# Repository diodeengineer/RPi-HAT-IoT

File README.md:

### RPi-HAT-IoT
A custom Raspberry Pi HAT designed for high-performance IoT applications. This board simplifies the integration of sensors and connectivity, turning a standard Raspberry Pi into a robust IoT Gateway or Edge device.

### Overview
This project provides a hardware-level expansion for the Raspberry Pi 40-pin header. It is designed to bridge the gap between physical sensors and cloud-based IoT platforms.

### Features
Form Factor: Standard Raspberry Pi HAT (compatible with Pi 3, 4, and 5).

Sensor Suite: (e.g., Temperature, Humidity, and Pressure sensors).

Indicator: Status LEDs for power and data transmission.

### 📂 Project Structure
/Hardware: KiCad schematic and PCB layout files.

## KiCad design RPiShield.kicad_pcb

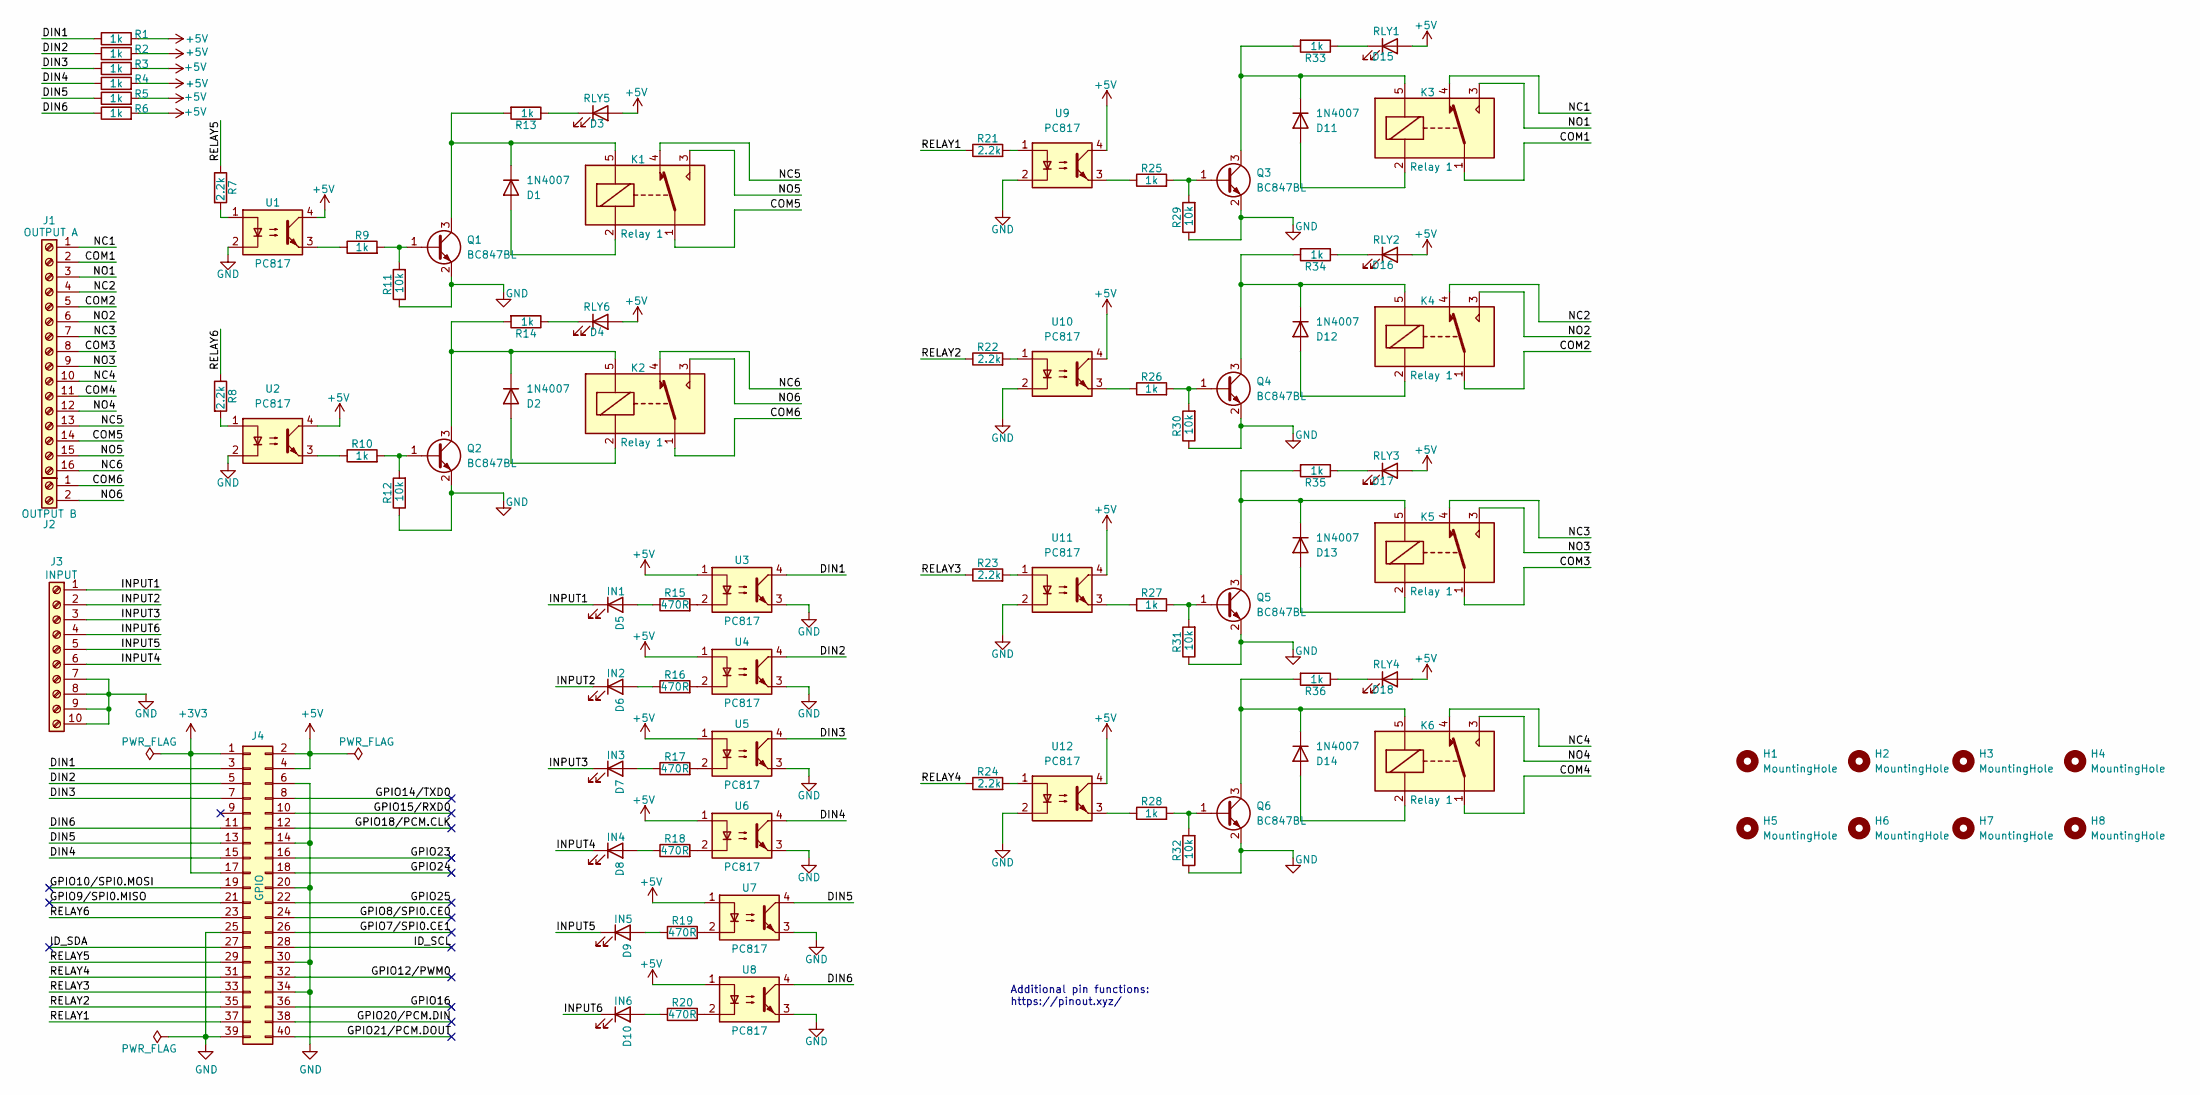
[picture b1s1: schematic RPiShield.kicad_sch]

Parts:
D1, D2, D11, D12, D13, D14: 1N4007; D_SMA_Handsoldering
D3: RLY5; LED_0805_2012Metric_Pad1.15x1.40mm_HandSolder
D4: RLY6; LED_0805_2012Metric_Pad1.15x1.40mm_HandSolder
D5: IN1; LED_0805_2012Metric_Pad1.15x1.40mm_HandSolder
D6: IN2; LED_0805_2012Metric_Pad1.15x1.40mm_HandSolder
D7: IN3; LED_0805_2012Metric_Pad1.15x1.40mm_HandSolder
D8: IN4; LED_0805_2012Metric_Pad1.15x1.40mm_HandSolder
D9: IN5; LED_0805_2012Metric_Pad1.15x1.40mm_HandSolder
D10: IN6; LED_0805_2012Metric_Pad1.15x1.40mm_HandSolder
D15: RLY1; LED_0805_2012Metric_Pad1.15x1.40mm_HandSolder
D16: RLY2; LED_0805_2012Metric_Pad1.15x1.40mm_HandSolder
D17: RLY3; LED_0805_2012Metric_Pad1.15x1.40mm_HandSolder
D18: RLY4; LED_0805_2012Metric_Pad1.15x1.40mm_HandSolder
H1, H2, H3, H4, H5, H6, H7, H8: MountingHole; MountingHole_2.7mm_M2.5
J1: OUTPUT A; TerminalBlock_Phoenix_MKDS-1,5-16_1x16_P5.00mm_Horizontal
J2: OUTPUT B; TerminalBlock_Phoenix_MKDS-1,5-2_1x02_P5.00mm_Horizontal
J3: INPUT; TerminalBlock_Phoenix_MKDS-1,5-10_1x10_P5.00mm_Horizontal
J4: GPIO; PinSocket_2x20_P2.54mm_Vertical
K1, K2, K3, K4, K5, K6: Relay 1; Relay_SPDT_Omron-G5LE-1
Q1, Q2, Q3, Q4, Q5, Q6: BC847BL; SOT-23
R1, R2, R3, R4, R5, R6, R9, R10, R13, R14, R25, R26, R27, R28, R33, R34, R35, R36: 1k; R_0805_2012Metric_Pad1.20x1.40mm_HandSolder
R7, R8, R21, R22, R23, R24: 2.2k; R_0805_2012Metric_Pad1.20x1.40mm_HandSolder
R11, R12, R29, R30, R31, R32: 10k; R_0805_2012Metric_Pad1.20x1.40mm_HandSolder
R15, R16, R17, R18, R19, R20: 470R; R_0805_2012Metric_Pad1.20x1.40mm_HandSolder
U1, U2, U3, U4, U5, U6, U7, U8, U9, U10, U11, U12: PC817; SOP259P1005X388-4N

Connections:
+3V3: J4.1, J4.17
+5V: D3.2 (A), D4.2 (A), D15.2 (A), D16.2 (A), D17.2 (A), D18.2 (A), J4.2, J4.4, R1.2, R2.2, R3.2, R4.2, R5.2, R6.2, U1.4, U2.4, U3.1, U4.1, U5.1, U6.1, U7.1, U8.1, U9.4, U10.4, U11.4, U12.4
/COM1: J1.2, K3.1
/COM2: J1.5, K4.1
/COM3: J1.8, K5.1
/COM4: J1.11, K6.1
/COM5: J1.14, K1.1
/COM6: J2.1, K2.1
/DIN1: J4.3, R1.1, U3.4
/DIN2: J4.5, R2.1, U4.4
/DIN3: J4.7, R3.1, U5.4
/DIN4: J4.15, R4.1, U6.4
/DIN5: J4.13, R5.1, U7.4
/DIN6: J4.11, R6.1, U8.4
/GPIO7/SPI0.CE1: J4.26
/GPIO8/SPI0.CE0: J4.24
/GPIO9/SPI0.MISO: J4.21
/GPIO10/SPI0.MOSI: J4.19
/GPIO12/PWM0: J4.32
/GPIO14/TXD0: J4.8
/GPIO15/RXD0: J4.10
/GPIO16: J4.36
/GPIO18/PCM.CLK: J4.12
/GPIO20/PCM.DIN: J4.38
/GPIO21/PCM.DOUT: J4.40
/GPIO23: J4.16
/GPIO24: J4.18
/GPIO25: J4.22
/ID_SCL: J4.28
/ID_SDA: J4.27
/INPUT1: D5.1 (K), J3.1
/INPUT2: D6.1 (K), J3.2
/INPUT3: D7.1 (K), J3.3
/INPUT4: D8.1 (K), J3.6
/INPUT5: D9.1 (K), J3.5
/INPUT6: D10.1 (K), J3.4
/NC1: J1.1, K3.4
/NC2: J1.4, K4.4
/NC3: J1.7, K5.4
/NC4: J1.10, K6.4
/NC5: J1.13, K1.4
/NC6: J1.16, K2.4
/NO1: J1.3, K3.3
/NO2: J1.6, K4.3
/NO3: J1.9, K5.3
/NO4: J1.12, K6.3
/NO5: J1.15, K1.3
/NO6: J2.2, K2.3
/RELAY1: J4.37, R21.1
/RELAY2: J4.35, R22.1
/RELAY3: J4.33, R23.1
/RELAY4: J4.31, R24.1
/RELAY5: J4.29, R7.1
/RELAY6: J4.23, R8.1
GND: J3.7, J3.8, J3.9, J3.10, J4.6, J4.14, J4.20, J4.25, J4.30, J4.34, J4.39, Q1.2 (E), Q2.2 (E), Q3.2 (E), Q4.2 (E), Q5.2 (E), Q6.2 (E), R11.1, R12.1, R29.1, R30.1, R31.1, R32.1, U1.2, U2.2, U3.3, U4.3, U5.3, U6.3, U7.3, U8.3, U9.2, U10.2, U11.2, U12.2
unnamed: D1.2 (A), K1.2
unnamed: D1.1 (K), K1.5, Q1.3 (C), R13.2
unnamed: D2.2 (A), K2.2
unnamed: D2.1 (K), K2.5, Q2.3 (C), R14.2
unnamed: D3.1 (K), R13.1
unnamed: D4.1 (K), R14.1
unnamed: D5.2 (A), R15.1
unnamed: D6.2 (A), R16.1
unnamed: D7.2 (A), R17.1
unnamed: D8.2 (A), R18.1
unnamed: D9.2 (A), R19.1
unnamed: D10.2 (A), R20.1
unnamed: D11.2 (A), K3.2
unnamed: D11.1 (K), K3.5, Q3.3 (C), R33.2
unnamed: D12.2 (A), K4.2
unnamed: D12.1 (K), K4.5, Q4.3 (C), R34.2
unnamed: D13.2 (A), K5.2
unnamed: D13.1 (K), K5.5, Q5.3 (C), R35.2
unnamed: D14.2 (A), K6.2
unnamed: D14.1 (K), K6.5, Q6.3 (C), R36.2
unnamed: D15.1 (K), R33.1
unnamed: D16.1 (K), R34.1
unnamed: D17.1 (K), R35.1
unnamed: D18.1 (K), R36.1
unnamed: Q1.1 (B), R9.2, R11.2
unnamed: Q2.1 (B), R10.2, R12.2
unnamed: Q3.1 (B), R25.2, R29.2
unnamed: Q4.1 (B), R26.2, R30.2
unnamed: Q5.1 (B), R27.2, R31.2
unnamed: Q6.1 (B), R28.2, R32.2
unnamed: R7.2, U1.1
unnamed: R8.2, U2.1
unnamed: R9.1, U1.3
unnamed: R10.1, U2.3
unnamed: R15.2, U3.2
unnamed: R16.2, U4.2
unnamed: R17.2, U5.2
unnamed: R18.2, U6.2
unnamed: R19.2, U7.2
unnamed: R20.2, U8.2
unnamed: R21.2, U9.1
unnamed: R22.2, U10.1
unnamed: R23.2, U11.1
unnamed: R24.2, U12.1
unnamed: R25.1, U9.3
unnamed: R26.1, U10.3
unnamed: R27.1, U11.3
unnamed: R28.1, U12.3

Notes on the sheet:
Additional pin functions: https://pinout.xyz/

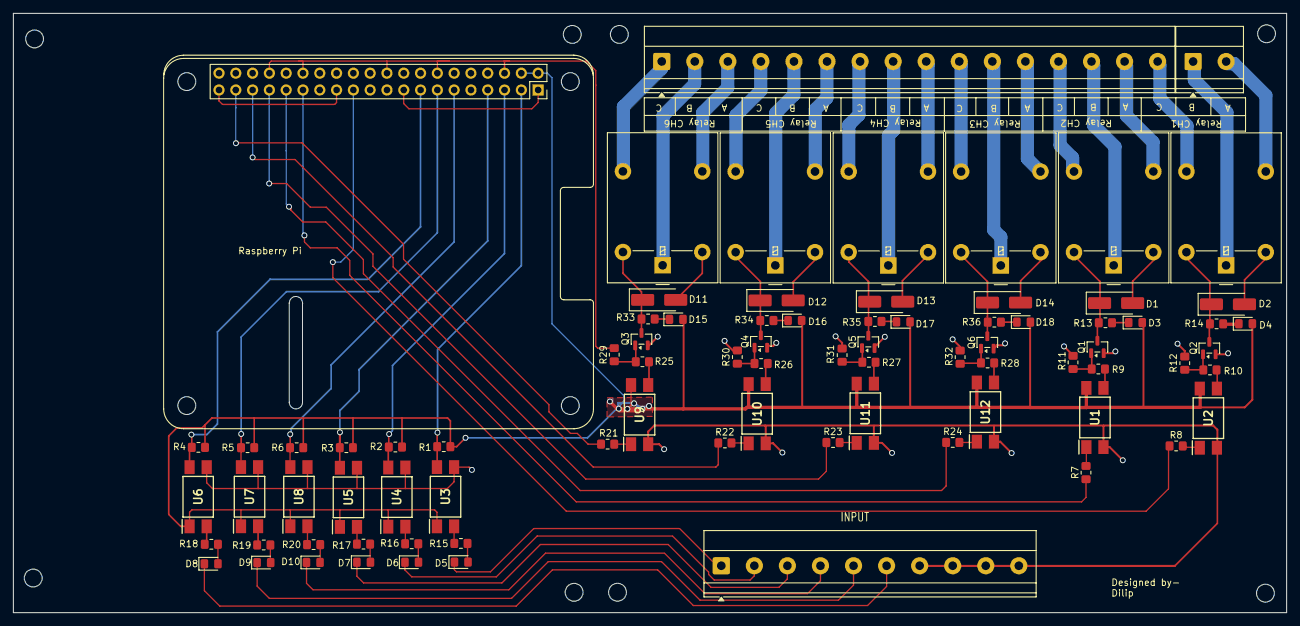
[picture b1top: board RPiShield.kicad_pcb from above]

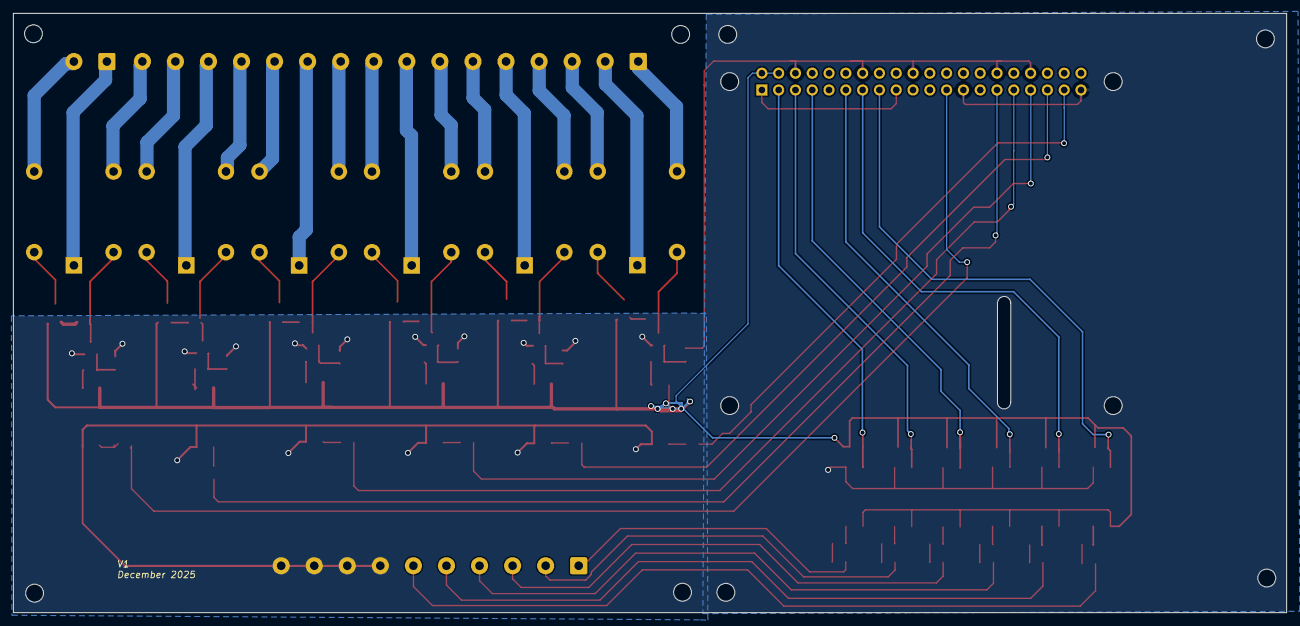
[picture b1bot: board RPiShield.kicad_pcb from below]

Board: 2 copper layers, 192.5 x 90.6 mm, 94 parts (4 on the bottom side), 87 nets.

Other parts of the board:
MH1, MH2, MH3, MH4: MountingHole_2.7mm_M2.5
